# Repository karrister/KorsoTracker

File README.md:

YAAT, an APRS Tracker
=============

This project is the HW design (PCB) for a ham radio APRS tracker. It takes input from GPS through UART, parsing the NMEA packets with location and speed info, making them into AX.25 frames and then converting that to physical layer data (analogic sound - at 1200 and 2200 khz).

There are many different APRS devices described on the internet but none of them were quite what I wanted. And afterall, ham radio is all about making your own devices!

73
OH2FLI

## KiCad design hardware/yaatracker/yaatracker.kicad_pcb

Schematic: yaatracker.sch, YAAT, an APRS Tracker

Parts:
C1, C2: 15pF
C3, C7: 0uF1
C4, C8: tbd
C5, C11, C12: 4uF7
C6: CSMALL
C9: 1uF
C10: 270nF
D1, D2: LED
D3: DIODE
D4: DIODESCH
D5: LED tbd
J1: USB_MINI
P1: TP_URX
P2: GPIO10_GND_JUMPER
P3: TP_UTX
P4: TON2
P5: RESET_CONN_2
P6: UART_TX_JUMPER
P7: MBUTTON3
P8: TP_TON1
P9: MBUTTON1
P10: BATT
P11: MBUTTON2
P12: ICSP_CONN5
P13: I2C_SCREEN
P14: R_VCC
P15: GPS_DE9
P16: RADIO_DE9
P17: SW5
Q1: DMP1045U
R1, R2: 60
R3, R12, R15: 4k7
R4, R6, R16, R17: 1k
R5, R7, R13, R14, R19: tbd
R8, R11: JUMPER
R9: 47k
R10: 100K
R18: 2k
RV1, RV2: 10k
T1: BSV52
U1: TPS769XX
U2: TLV271
U3: PIC18F14K50
U4: MCP7383X
X1: 10MHz

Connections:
+3.3V: C5.1, C6.2, C8.1, P7.2 (PM), P9.2 (PM), P11.2 (PM), P12.2, P13.1, P15.1, P17.2 (PM), R1.1, R2.1, R3.1, R12.2, R15.2, RV1.1, U1.5 (OUT), U2.5 (Vdd), U3.1 (Vdd)
/AUDIO_IN: C3.2, P16.2
/AUDIO_OUT: P4.1, P16.3, RV2.2
/PTT: P16.1, T1.3 (C)
/R_VOUT: P14.2 (PM), P16.5
/UART_RX: P1.1, P15.4, U3.12 (RB5/AN11/RX)
/UART_TX: P3.1, P6.2 (PM), P15.3
GND: C1.1, C2.1, C4.2, C5.2, C6.1, C7.2, C8.2, C9.2, C10.1, C11.2, C12.2, J1.5 (GND), P2.1, P5.1, P10.2 (PM), P12.3, P13.2, P15.2, P16.4, R6.1, R10.2, R16.1, R17.1, R18.1, RV1.3, RV2.3, T1.2 (E), U1.2 (GND), U1.3 (EN), U2.2 (GND), U3.20 (Vss), U4.2 (Vss)
unnamed: D1.1 (A), R1.2
unnamed: D2.1 (A), R2.2
unnamed: D3.1 (A), R3.2
unnamed: C4.1, R5.1, RV2.1
unnamed: D1.2 (K), U3.6 (RC4/P1B)
unnamed: D3.2 (K), P5.2 (PM), P12.1, U3.4 (RA3/MCLR)
unnamed: R9.1, U3.8 (RC6/AN8/SS)
unnamed: P11.1, R14.2, R17.2
unnamed: P9.1, R13.2, R16.2
unnamed: R7.1, U3.7 (RC3/AN7)
unnamed: C7.1, R9.2, T1.1 (B)
unnamed: D2.2 (K), U3.5 (RC5/CCP1)
unnamed: P7.1, R4.1
unnamed: P2.2 (PM), P6.1, R4.2, U3.10 (RB7/TX)
unnamed: R14.1, U3.15 (RC1/AN5/INT1)
unnamed: R13.1, U3.16 (RC0/AN4/INT0)
unnamed: C3.1, RV1.2, U3.9 (RC7/AN9/SDO)
unnamed: P17.1, R6.2, R7.2
unnamed: C10.2, U3.17 (VUSB)
unnamed: J1.3 (D+), P12.4, U3.19 (RA0/D+)
unnamed: J1.2 (D-), P12.5, U3.18 (RA1/D-)
unnamed: C9.1, D4.2 (K), Q1.S, U1.1 (IN)
unnamed: R11.1, U2.4 (-IN)
unnamed: R8.2, U2.1 (OUT)
unnamed: R5.2, R8.1, R11.2
unnamed: C11.1, P10.1, Q1.D, U4.3 (Vbat)
unnamed: R18.2, U4.5 (PROG)
unnamed: C2.2, U3.2 (RA5/OSC1), X1.2
unnamed: C1.2, U3.3 (RA4/OSC2), X1.1
unnamed: C12.1, D4.1 (A), J1.1 (VBUS), P14.1, Q1.G, R10.1, R19.2, U4.4 (Vdd)
unnamed: D5.2 (K), U4.1 (STAT)
unnamed: D5.1 (A), R19.1
unnamed: P13.3, R12.1, U3.11 (RB6/SCK)
unnamed: P13.4, R15.1, U3.13 (RB4/AN10/SDI/SDA)
unnamed: P8.1, U2.3 (+IN), U3.14 (RC2/AN6/INT2)

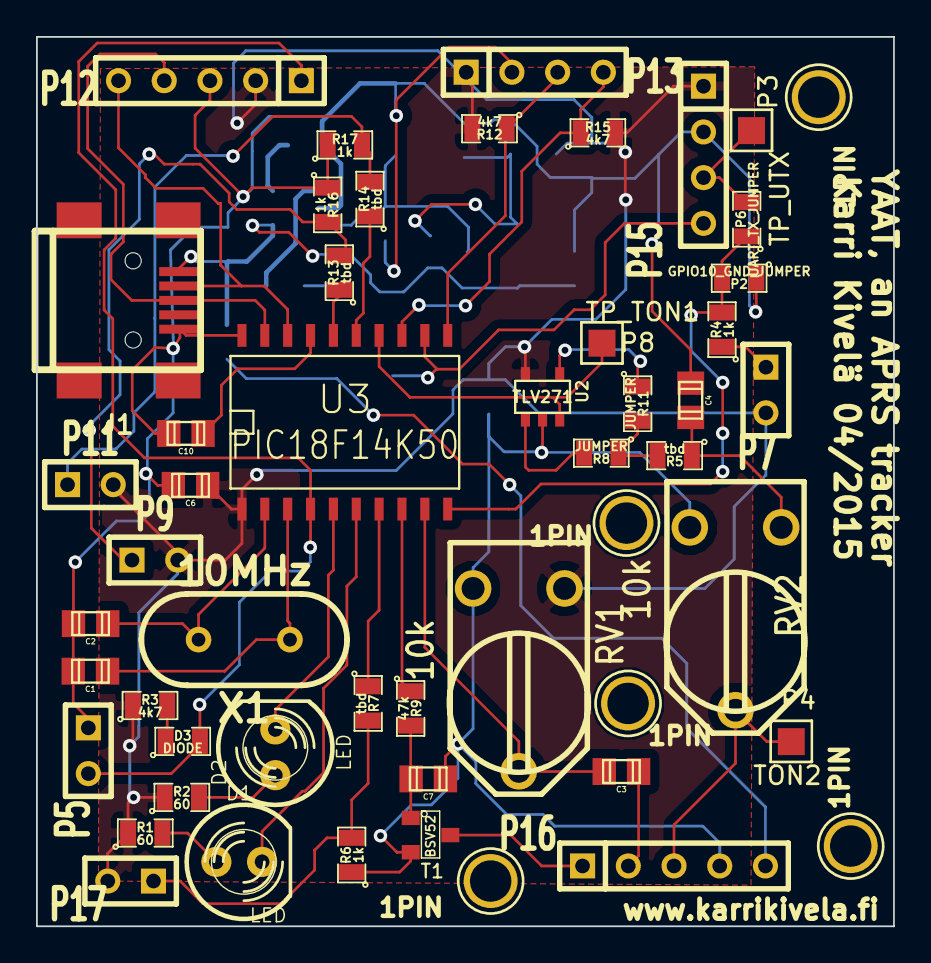
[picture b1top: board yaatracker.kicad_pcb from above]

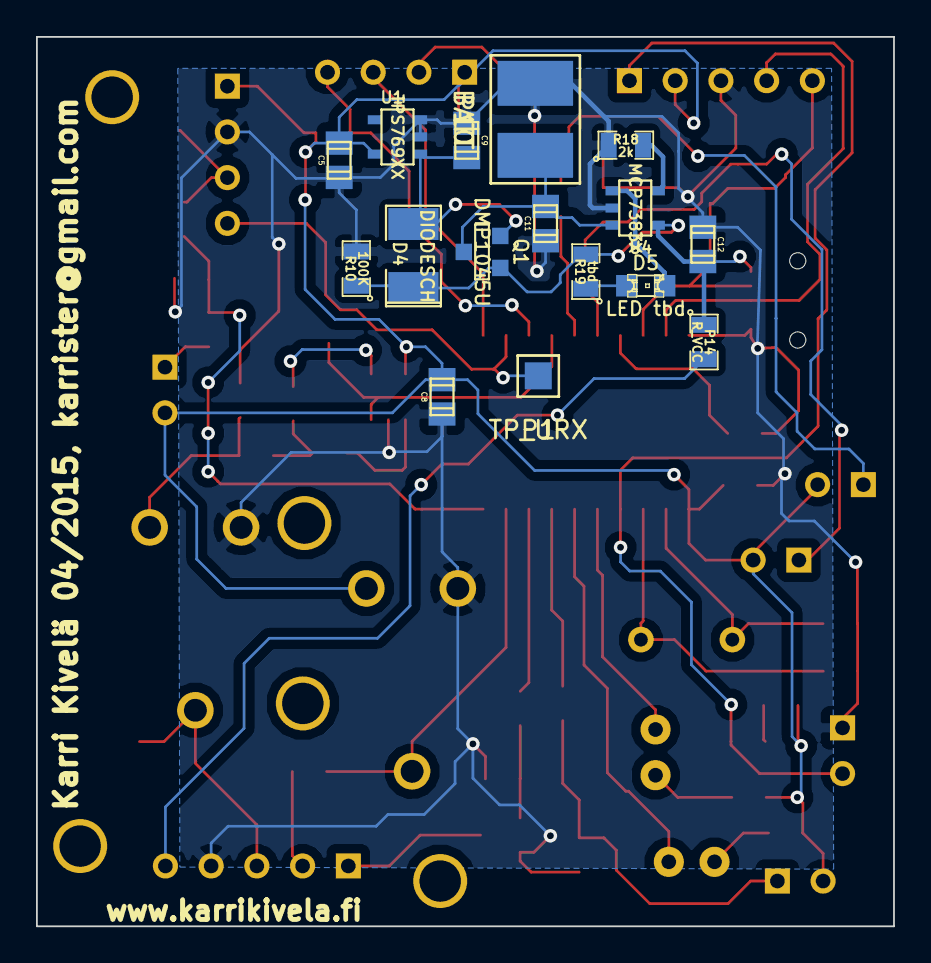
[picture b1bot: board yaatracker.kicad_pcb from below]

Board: 2 copper layers, 47.6 x 49.4 mm, 68 parts (16 on the bottom side), 43 nets.

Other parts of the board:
1PIN, 1PIN#2, 1PIN#3, 1PIN#4, 1PIN#5: P***; 1pin

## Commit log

2015-04-18 :boom::camel: Added .gitattributes
2015-04-18 Initial commit
    Initial commit with the README file, and the kicad project file for the
    pcb design project.
2015-04-18 Schematics started
    Schematics started, power supply line ready. Committing library from my
    other BT project
2015-04-18 Schematics op amp
    Schematics drawing now with op amp to audio out
2015-04-18 Schematics + License
    Schematics support now ICSP connector.
    Also the license file added.
2015-04-18 More work on schematics
    Now supporting PIC oscillator, jumper line for UART TX and audio
    in/carrier detect.
2015-04-18 Schematics mostly done
    Schematics are only lacking 2 LEDs and all the buttons and a switch.
    Also need to revisit the USB connection.
2015-04-19 Renaming project
2015-04-19 Renaming project
    Continuing to rename project
2015-04-19 Restructuring directories
2015-04-19 Schematics before check
    Schematics are ready to be checked.
2015-04-19 Schematics work
    Working to get a good pcb
2015-04-20 SCHEMATICS DONE
    Schematics should be now ready.
2015-04-20 Schematics after ERC
    Some fixes after ERC. ERC still complains but only warnings - nothing
    serious that would need to be fixed for now.
2015-04-23 Netlist generated
    Netlist generated, footprints for parts chosen.
2015-04-24 PCB layout power circuit
    Started the power circuit layout of the PCB.
2015-04-24 PCB layout power circuit finished
    Layout of the power circuit is now finished
2015-04-24 More PCB layout
    ICSP connector done, as well as screen/I2C connector, and a few buttons.
2015-04-24 Some more PCB layout
    Some more PCB layout. Forgot to connect two grounds together.
2015-04-24 Traces to GPS conn, audio out
    Routed traces to GPS uart connector, and audio out done to pot.
2015-04-24 PCB layout almost finished
    Lacking LEDs, and a few buttons to be routed.
2015-04-24 PCB layout routing done
    PCB layout traces routing done, but need to add a button connected to pin 7 (pull down
    and current-limiting resistor already exist in design).
2015-04-24 PCB layout last switch
    Added and routed another switch successfully.
2015-04-24 PCB in the last stage
    Layout done otherwise but need to see if can fix the "unconnected pad"
    error - for some reason USB connector shield wants to be connected to a
    data pin...
2015-04-24 PCB design finished. Gerber files ready.
    PCB design is done, and gerber files have been generated.
2015-04-24 PCB version 1.0
    PCB done, ready for printing. PCB version 1.0.
